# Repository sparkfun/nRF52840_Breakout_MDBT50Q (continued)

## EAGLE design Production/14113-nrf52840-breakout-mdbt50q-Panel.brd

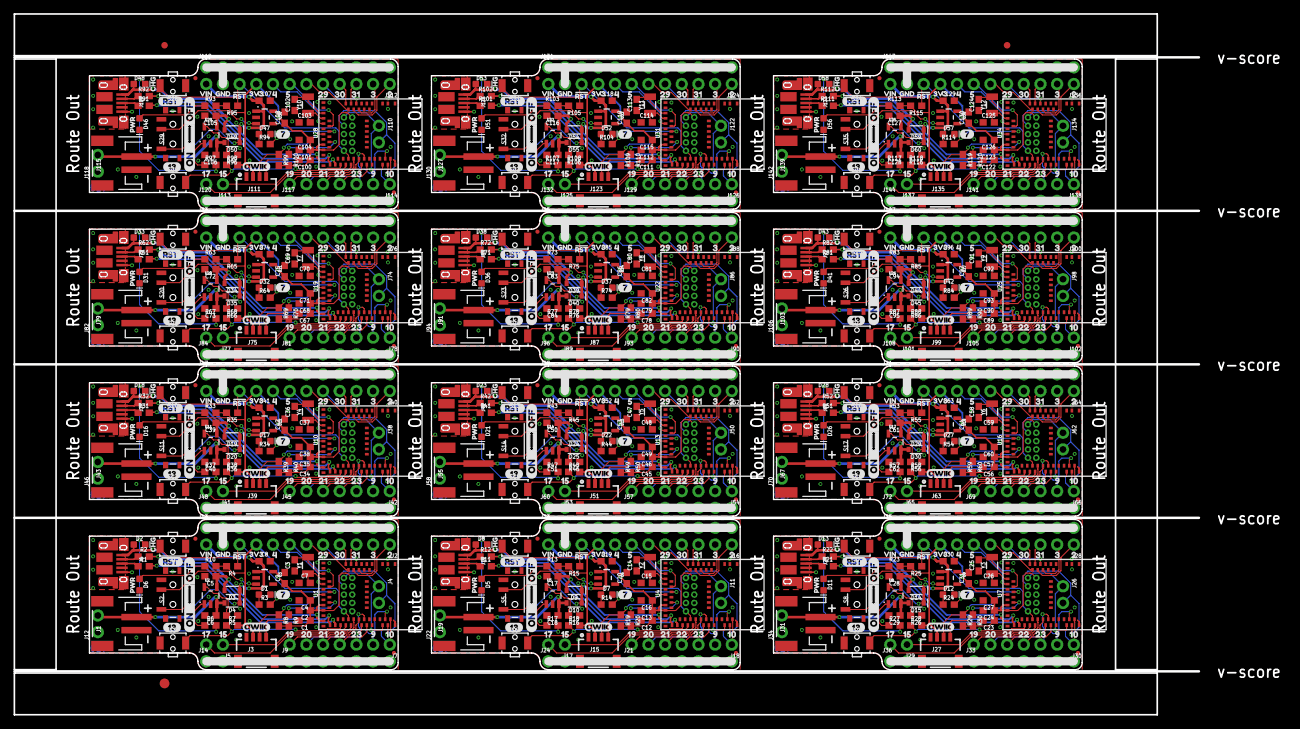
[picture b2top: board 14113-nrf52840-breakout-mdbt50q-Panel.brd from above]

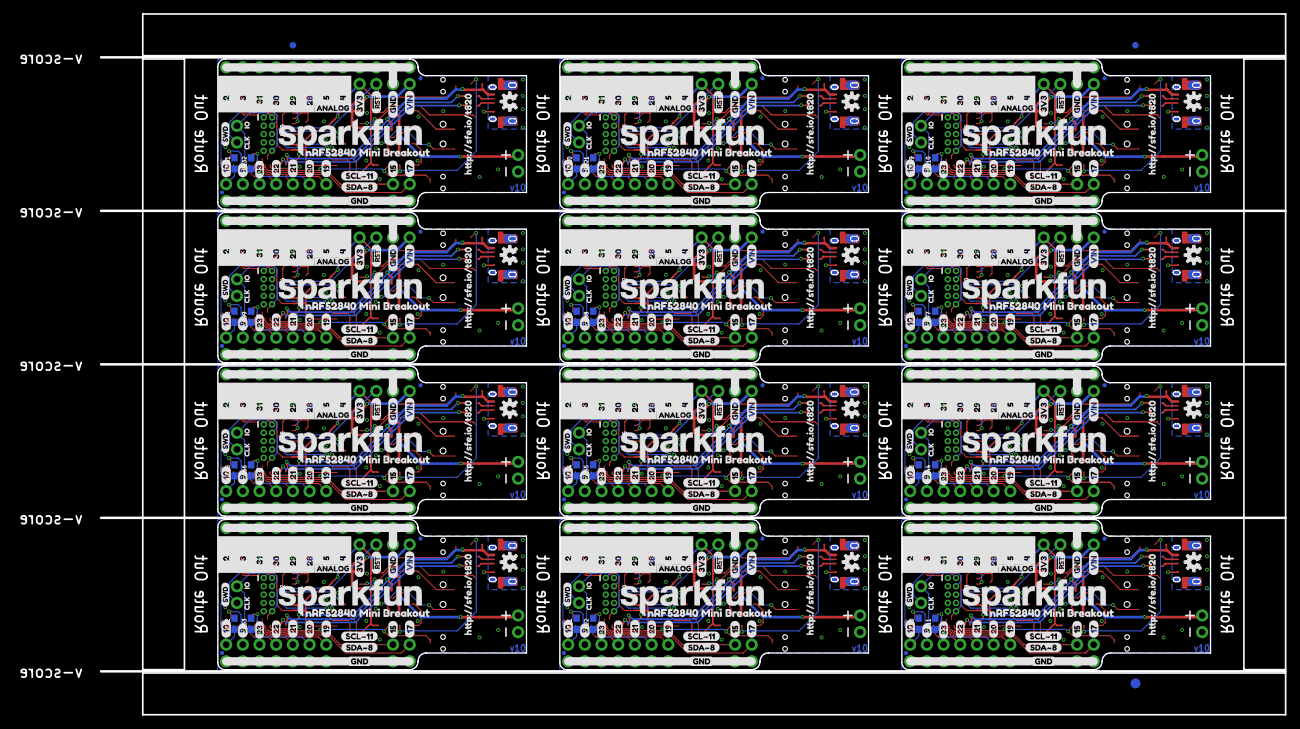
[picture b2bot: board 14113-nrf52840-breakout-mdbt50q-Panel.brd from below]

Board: 2 copper layers, 180.3 x 106.7 mm, 1314 parts (447 on the bottom side), 504 nets.

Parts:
C1, C4, C12, C16, C23, C27, C34, C38, C45, C49, C56, C60, C67, C71, C78, C82, C89, C93, C100, C104, C111, C115, C122, C126: 10uF; 0603
C2, C13, C24, C35, C46, C57, C68, C79, C90, C101, C112, C123: 0.1uF; 0603
C3, C7, C14, C15, C25, C26, C36, C37, C47, C48, C58, C59, C69, C70, C80, C81, C91, C92, C102, C103, C113, C114, C124, C125: 15pF; 0603
C5, C6, C17, C18, C28, C29, C39, C40, C50, C51, C61, C62, C72, C73, C83, C84, C94, C95, C105, C106, C116, C117, C127, C128: 4.7uF; 0603
C8, C9, C19, C20, C30, C31, C41, C42, C52, C53, C63, C64, C74, C75, C85, C86, C96, C97, C107, C108, C118, C119, C129, C130: 1.0uF; 0603
C10, C11, C21, C22, C32, C33, C43, C44, C54, C55, C65, C66, C76, C77, C87, C88, C98, C99, C109, C110, C120, C121, C131, C132: DNP; 0603
D1, D7, D12, D17, D22, D27, D32, D37, D42, D47, D52, D57: BLUE; LED-0603
D2, D8, D13, D18, D23, D28, D33, D38, D43, D48, D53, D58: Yellow; LED-0603
D3, D4, D9, D10, D14, D15, D19, D20, D24, D25, D29, D30, D34, D35, D39, D40, D44, D45, D49, D50, D54, D55, D59, D60: 1A/23V/620mV; SOD-323
D5, D6, D11, D16, D21, D26, D31, D36, D41, D46, D51, D56: RED; LED-0603
E$1, E$2, E$3, E$4: FIDUCIAL-1X2
E$5, E$6: FIDUCIAL-1.5X3
FD1, FD2, FD3, FD4, FD5, FD6, FD7, FD8, FD9, FD10, FD11, FD12, FD13, FD14, FD15, FD16, FD17, FD18, FD19, FD20, FD21, FD22, FD23, FD24, FD25, FD26, FD27, FD28, FD29, FD30, FD31, FD32, FD33, FD34, FD35, FD36, FD37, FD38, FD39, FD40, FD41, FD42, FD43, FD44, FD45, FD46, FD47, FD48: FIDUCIALUFIDUCIAL; FIDUCIAL-MICRO
J1, J19, J31, J43, J55, J67, J79, J91, J103, J115, J127, J139: JST-2-SMD
J2, J13, J16, J23, J28, J35, J40, J47, J52, J59, J64, J71, J76, J83, J88, J95, J100, J107, J112, J119, J124, J131, J136, J143: 1X12_NO_SILK
J3, J15, J27, J39, J51, J63, J75, J87, J99, J111, J123, J135: 1X04_1MM_RA
J4, J5, J11, J12, J14, J17, J22, J24, J26, J29, J34, J36, J38, J41, J46, J48, J50, J53, J58, J60, J62, J65, J70, J72, J74, J77, J82, J84, J86, J89, J94, J96, J98, J101, J106, J108, J110, J113, J118, J120, J122, J125, J130, J132, J134, J137, J142, J144: 1X02_NO_SILK
J6, J10, J25, J37, J49, J61, J73, J85, J97, J109, J121, J133: USB-MICROB-PTH-MILL
J7, J9, J18, J21, J30, J33, J42, J45, J54, J57, J66, J69, J78, J81, J90, J93, J102, J105, J114, J117, J126, J129, J138, J141: 1X07_NO_SILK
J8, J20, J32, J44, J56, J68, J80, J92, J104, J116, J128, J140: CORTEX_DEBUG_PTH; 2X5-PTH-1.27MM
LOGO1, LOGO3, LOGO5, LOGO7, LOGO9, LOGO11, LOGO13, LOGO15, LOGO17, LOGO19, LOGO21, LOGO23: SFE_LOGO_NAME.2_INCH; SFE_LOGO_NAME_.2
LOGO2, LOGO4, LOGO6, LOGO8, LOGO10, LOGO12, LOGO14, LOGO16, LOGO18, LOGO20, LOGO22, LOGO24: OSHW-LOGOS; OSHW-LOGO-S
R1, R2, R11, R12, R21, R22, R31, R32, R41, R42, R51, R52, R61, R62, R71, R72, R81, R82, R91, R92, R101, R102, R111, R112: 27; 0603
R3, R6, R10, R13, R14, R17, R23, R24, R27, R33, R34, R37, R43, R44, R47, R53, R54, R57, R63, R64, R67, R73, R74, R77, R83, R84, R87, R93, R94, R97, R103, R104, R107, R113, R114, R117: 1k; 0603
R4, R7, R15, R18, R25, R28, R35, R38, R45, R48, R55, R58, R65, R68, R75, R78, R85, R88, R95, R98, R105, R108, R115, R118: 10k; 0603
R5, R16, R26, R36, R46, R56, R66, R76, R86, R96, R106, R116: 2.0k; 0603
R8, R9, R19, R20, R29, R30, R39, R40, R49, R50, R59, R60, R69, R70, R79, R80, R89, R90, R99, R100, R109, R110, R119, R120: 2.2k; 0603
S1, S4, S7, S10, S13, S16, S19, S22, S25, S28, S31, S34: RESET; TACTILE_SWITCH_SMD_RIGHT_ANGLE
S2, S5, S8, S11, S14, S17, S20, S23, S26, S29, S32, S35: SWITCH_SPST_SMD_A
S3, S6, S9, S12, S15, S18, S21, S24, S27, S30, S33, S36: BOOTLOAD; TACTILE_SWITCH_SMD_RIGHT_ANGLE
U1, U4, U7, U10, U13, U16, U19, U22, U25, U28, U31, U34: MDBT50Q
U2, U5, U8, U11, U14, U17, U20, U23, U26, U29, U32, U35: MCP73831; SOT23-5
U3, U6, U9, U12, U15, U18, U21, U24, U27, U30, U33, U36: 3.3V; SOT23-5
U$1, U$92, U$150, U$208, U$266, U$324, U$382, U$440, U$498, U$556, U$614, U$672: 3V316
U$2, U$109, U$167, U$225, U$283, U$341, U$399, U$457, U$515, U$573, U$631, U$689: 130
U$3, U$91, U$149, U$207, U$265, U$323, U$381, U$439, U$497, U$555, U$613, U$671: RST19
U$4, U$113, U$171, U$229, U$287, U$345, U$403, U$461, U$519, U$577, U$635, U$693: ON1
U$5, U$59, U$117, U$175, U$233, U$291, U$349, U$407, U$465, U$523, U$581, U$639: CHG26
U$6, U$60, U$118, U$176, U$234, U$292, U$350, U$408, U$466, U$524, U$582, U$640: PWR27
U$7, U$89, U$147, U$205, U$263, U$321, U$379, U$437, U$495, U$553, U$611, U$669: GND17
U$8, U$87, U$145, U$203, U$261, U$319, U$377, U$435, U$493, U$551, U$609, U$667: QWIIC#LOGO#JPG
U$9, U$62, U$120, U$178, U$236, U$294, U$352, U$410, U$468, U$526, U$584, U$642: 20
U$10, U$63, U$121, U$179, U$237, U$295, U$353, U$411, U$469, U$527, U$585, U$643: 31
U$11, U$64, U$122, U$180, U$238, U$296, U$354, U$412, U$470, U$528, U$586, U$644: 292
U$12, U$65, U$123, U$181, U$239, U$297, U$355, U$413, U$471, U$529, U$587, U$645: 313
U$13, U$111, U$169, U$227, U$285, U$343, U$401, U$459, U$517, U$575, U$633, U$691: 3V30
U$14, U$66, U$124, U$182, U$240, U$298, U$356, U$414, U$472, U$530, U$588, U$646: 285
U$15, U$67, U$125, U$183, U$241, U$299, U$357, U$415, U$473, U$531, U$589, U$647: 521
U$16, U$68, U$126, U$184, U$242, U$300, U$358, U$416, U$474, U$532, U$590, U$648: 421
U$17, U$112, U$170, U$228, U$286, U$344, U$402, U$460, U$518, U$576, U$634, U$692: HTTP###SFE#IO#T8200
U$18, U$69, U$127, U$185, U$243, U$301, U$359, U$417, U$475, U$533, U$591, U$649: #RST6
U$19, U$70, U$128, U$186, U$244, U$302, U$360, U$418, U$476, U$534, U$592, U$650: GND7
U$20, U$71, U$129, U$187, U$245, U$303, U$361, U$419, U$477, U$535, U$593, U$651: VIN8
U$21, U$72, U$130, U$188, U$246, U$304, U$362, U$420, U$478, U$536, U$594, U$652: 1022
U$22, U$73, U$131, U$189, U$247, U$305, U$363, U$421, U$479, U$537, U$595, U$653: 916
U$23, U$74, U$132, U$190, U$248, U$306, U$364, U$422, U$480, U$538, U$596, U$654: 2111
U$24, U$75, U$133, U$191, U$249, U$307, U$365, U$423, U$481, U$539, U$597, U$655: 1912
U$25, U$76, U$134, U$192, U$250, U$308, U$366, U$424, U$482, U$540, U$598, U$656: 1713
U$26, U$77, U$135, U$193, U$251, U$309, U$367, U$425, U$483, U$541, U$599, U$657: 1522
U$27, U$90, U$148, U$206, U$264, U$322, U$380, U$438, U$496, U$554, U$612, U$670: VIN19
U$28, U$88, U$146, U$204, U$262, U$320, U$378, U$436, U$494, U$552, U$610, U$668: 70
U$29, U$86, U$144, U$202, U$260, U$318, U$376, U$434, U$492, U$550, U$608, U$666: NRF52840_MINI_BREAKOUT0
U$30, U$61, U$119, U$177, U$235, U$293, U$351, U$409, U$467, U$525, U$583, U$641: GND6
U$31, U$93, U$151, U$209, U$267, U$325, U$383, U$441, U$499, U$557, U$615, U$673: 27
U$32, U$94, U$152, U$210, U$268, U$326, U$384, U$442, U$500, U$558, U$616, U$674: 36
U$33, U$83, U$141, U$199, U$257, U$315, U$373, U$431, U$489, U$547, U$605, U$663: SWD0
U$34, U$95, U$153, U$211, U$269, U$327, U$385, U$443, U$501, U$559, U$617, U$675: 315
U$35, U$110, U$168, U$226, U$284, U$342, U$400, U$458, U$516, U$574, U$632, U$690: 300
U$36, U$116, U$174, U$232, U$290, U$348, U$406, U$464, U$522, U$580, U$638, U$696: 301
U$37, U$96, U$154, U$212, U$270, U$328, U$386, U$444, U$502, U$560, U$618, U$676: 293
U$38, U$99, U$157, U$215, U$273, U$331, U$389, U$447, U$505, U$563, U$621, U$679: 108
U$39, U$97, U$155, U$213, U$271, U$329, U$387, U$445, U$503, U$561, U$619, U$677: 51
U$40, U$98, U$156, U$214, U$272, U$330, U$388, U$446, U$504, U$562, U$620, U$678: 40
U$41, U$100, U$158, U$216, U$274, U$332, U$390, U$448, U$506, U$564, U$622, U$680: 97
U$42, U$101, U$159, U$217, U$275, U$333, U$391, U$449, U$507, U$565, U$623, U$681: 236
U$43, U$78, U$136, U$194, U$252, U$310, U$368, U$426, U$484, U$542, U$600, U$658: 200
U$44, U$102, U$160, U$218, U$276, U$334, U$392, U$450, U$508, U$566, U$624, U$682: 225
U$45, U$79, U$137, U$195, U$253, U$311, U$369, U$427, U$485, U$543, U$601, U$659: 221
U$46, U$103, U$161, U$219, U$277, U$335, U$393, U$451, U$509, U$567, U$625, U$683: 214
U$47, U$104, U$162, U$220, U$278, U$336, U$394, U$452, U$510, U$568, U$626, U$684: 203
U$48, U$105, U$163, U$221, U$279, U$337, U$395, U$453, U$511, U$569, U$627, U$685: 192
U$49, U$106, U$164, U$222, U$280, U$338, U$396, U$454, U$512, U$570, U$628, U$686: 151
U$50, U$107, U$165, U$223, U$281, U$339, U$397, U$455, U$513, U$571, U$629, U$687: 170
U$51, U$108, U$166, U$224, U$282, U$340, U$398, U$456, U$514, U$572, U$630, U$688: RST1
U$52, U$115, U$173, U$231, U$289, U$347, U$405, U$463, U$521, U$579, U$637, U$695: ANALOG2
U$53, U$80, U$138, U$196, U$254, U$312, U$370, U$428, U$486, U$544, U$602, U$660: 232
U$54, U$81, U$139, U$197, U$255, U$313, U$371, U$429, U$487, U$545, U$603, U$661: SCL#114
U$55, U$82, U$140, U$198, U$256, U$314, U$372, U$430, U$488, U$546, U$604, U$662: SDA#83
U$56, U$84, U$142, U$200, U$258, U$316, U$374, U$432, U$490, U$548, U$606, U$664: IO2
U$57, U$85, U$143, U$201, U$259, U$317, U$375, U$433, U$491, U$549, U$607, U$665: CLK1
U$58, U$114, U$172, U$230, U$288, U$346, U$404, U$462, U$520, U$578, U$636, U$694: OFF2
Y1, Y2, Y3, Y4, Y5, Y6, Y7, Y8, Y9, Y10, Y11, Y12: 32.768kHz; CRYSTAL-SMD-3.2X1.5MM

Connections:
3.3V: C1.1, C2.1, C4.1, C9.1, J2.9, J3.2, J8.1, R4.2, R7.2, R8.2, R9.2, R10.2, U1.28, U1.30, U3.5
3.3V1: C12.1, C13.1, C16.1, C20.1, J15.2, J16.9, J20.1, R13.2, R15.2, R18.2, R19.2, R20.2, U4.28, U4.30, U6.5
3.3V2: C23.1, C24.1, C27.1, C31.1, J27.2, J28.9, J32.1, R23.2, R25.2, R28.2, R29.2, R30.2, U7.28, U7.30, U9.5
3.3V3: C34.1, C35.1, C38.1, C42.1, J39.2, J40.9, J44.1, R33.2, R35.2, R38.2, R39.2, R40.2, U10.28, U10.30, U12.5
3.3V4: C45.1, C46.1, C49.1, C53.1, J51.2, J52.9, J56.1, R43.2, R45.2, R48.2, R49.2, R50.2, U13.28, U13.30, U15.5
3.3V5: C56.1, C57.1, C60.1, C64.1, J63.2, J64.9, J68.1, R53.2, R55.2, R58.2, R59.2, R60.2, U16.28, U16.30, U18.5
3.3V6: C67.1, C68.1, C71.1, C75.1, J75.2, J76.9, J80.1, R63.2, R65.2, R68.2, R69.2, R70.2, U19.28, U19.30, U21.5
3.3V7: C78.1, C79.1, C82.1, C86.1, J87.2, J88.9, J92.1, R73.2, R75.2, R78.2, R79.2, R80.2, U22.28, U22.30, U24.5
3.3V8: C89.1, C90.1, C93.1, C97.1, J99.2, J100.9, J104.1, R83.2, R85.2, R88.2, R89.2, R90.2, U25.28, U25.30, U27.5
3.3V9: C100.1, C101.1, C104.1, C108.1, J111.2, J112.9, J116.1, R93.2, R95.2, R98.2, R99.2, R100.2, U28.28, U28.30, U30.5
3.3V10: C111.1, C112.1, C115.1, C119.1, J123.2, J124.9, J128.1, R103.2, R105.2, R108.2, R109.2, R110.2, U31.28, U31.30, U33.5
3.3V11: C122.1, C123.1, C126.1, C130.1, J135.2, J136.9, J140.1, R113.2, R115.2, R118.2, R119.2, R120.2, U34.28, U34.30, U36.5
!RESET: J2.10, J8.10, R4.1, S1.2, U1.40
!RESET1: J16.10, J20.10, R15.1, S4.2, U4.40
!RESET2: J28.10, J32.10, R25.1, S7.2, U7.40
!RESET3: J40.10, J44.10, R35.1, S10.2, U10.40
!RESET4: J52.10, J56.10, R45.1, S13.2, U13.40
!RESET5: J64.10, J68.10, R55.1, S16.2, U16.40
!RESET6: J76.10, J80.10, R65.1, S19.2, U19.40
!RESET7: J88.10, J92.10, R75.1, S22.2, U22.40
!RESET8: J100.10, J104.10, R85.1, S25.2, U25.40
!RESET9: J112.10, J116.10, R95.1, S28.2, U28.40
!RESET10: J124.10, J128.10, R105.1, S31.2, U31.40
!RESET11: J136.10, J140.10, R115.1, S34.2, U34.40
D+: R1.2, U1.35
D+1: R11.2, U4.35
D+2: R21.2, U7.35
D+3: R31.2, U10.35
D+4: R41.2, U13.35
D+5: R51.2, U16.35
D+6: R61.2, U19.35
D+7: R71.2, U22.35
D+8: R81.2, U25.35
D+9: R91.2, U28.35
D+10: R101.2, U31.35
D+11: R111.2, U34.35
D+_CON: J6.D+, R1.1
D+_CON1: J10.D+, R11.1
D+_CON2: J25.D+, R21.1
D+_CON3: J37.D+, R31.1
D+_CON4: J49.D+, R41.1
D+_CON5: J61.D+, R51.1
D+_CON6: J73.D+, R61.1
D+_CON7: J85.D+, R71.1
D+_CON8: J97.D+, R81.1
D+_CON9: J109.D+, R91.1
D+_CON10: J121.D+, R101.1
D+_CON11: J133.D+, R111.1
D-: R2.2, U1.34
D-1: R12.2, U4.34
D-2: R22.2, U7.34
D-3: R32.2, U10.34
D-4: R42.2, U13.34
D-5: R52.2, U16.34
D-6: R62.2, U19.34
D-7: R72.2, U22.34
D-8: R82.2, U25.34
D-9: R92.2, U28.34
D-10: R102.2, U31.34
D-11: R112.2, U34.34
D-_CON: J6.D-, R2.1
D-_CON1: J10.D-, R12.1
D-_CON2: J25.D-, R22.1
D-_CON3: J37.D-, R32.1
D-_CON4: J49.D-, R42.1
D-_CON5: J61.D-, R52.1
D-_CON6: J73.D-, R62.1
D-_CON7: J85.D-, R72.1
D-_CON8: J97.D-, R82.1
D-_CON9: J109.D-, R92.1
D-_CON10: J121.D-, R102.1
D-_CON11: J133.D-, R112.1
GND: C1.2, C2.2, C3.1, C4.2, C5.2, C6.2, C7.1, C8.2, C9.2, C10.2, C11.2, D1.C, D6.C, J1.1, J2.11, J3.1, J6.GND, J8.3, J8.5, J8.9, J9.1, J9.2, J9.3, J9.4, J9.5, J9.6, J9.7, J12.1, J13.1, J13.2, J13.3, J13.4, J13.5, J13.6, J13.7, J13.8, J13.9, J13.10, J13.11, J13.12, J14.1, J14.2, R5.1, S1.1, S2.1, S3.1, U1.1, U1.2, U1.15, U1.33, U1.55, U2.2, U3.2
GND1: C12.2, C13.2, C14.1, C15.1, C16.2, C17.2, C18.2, C19.2, C20.2, C21.2, C22.2, D5.C, D7.C, J10.GND, J15.1, J16.11, J19.1, J20.3, J20.5, J20.9, J21.1, J21.2, J21.3, J21.4, J21.5, J21.6, J21.7, J22.1, J23.1, J23.2, J23.3, J23.4, J23.5, J23.6, J23.7, J23.8, J23.9, J23.10, J23.11, J23.12, J24.1, J24.2, R16.1, S4.1, S5.1, S6.1, U4.1, U4.2, U4.15, U4.33, U4.55, U5.2, U6.2
GND2: C23.2, C24.2, C25.1, C26.1, C27.2, C28.2, C29.2, C30.2, C31.2, C32.2, C33.2, D11.C, D12.C, J25.GND, J27.1, J28.11, J31.1, J32.3, J32.5, J32.9, J33.1, J33.2, J33.3, J33.4, J33.5, J33.6, J33.7, J34.1, J35.1, J35.2, J35.3, J35.4, J35.5, J35.6, J35.7, J35.8, J35.9, J35.10, J35.11, J35.12, J36.1, J36.2, R26.1, S7.1, S8.1, S9.1, U7.1, U7.2, U7.15, U7.33, U7.55, U8.2, U9.2
GND3: C34.2, C35.2, C36.1, C37.1, C38.2, C39.2, C40.2, C41.2, C42.2, C43.2, C44.2, D16.C, D17.C, J37.GND, J39.1, J40.11, J43.1, J44.3, J44.5, J44.9, J45.1, J45.2, J45.3, J45.4, J45.5, J45.6, J45.7, J46.1, J47.1, J47.2, J47.3, J47.4, J47.5, J47.6, J47.7, J47.8, J47.9, J47.10, J47.11, J47.12, J48.1, J48.2, R36.1, S10.1, S11.1, S12.1, U10.1, U10.2, U10.15, U10.33, U10.55, U11.2, U12.2
GND4: C45.2, C46.2, C47.1, C48.1, C49.2, C50.2, C51.2, C52.2, C53.2, C54.2, C55.2, D21.C, D22.C, J49.GND, J51.1, J52.11, J55.1, J56.3, J56.5, J56.9, J57.1, J57.2, J57.3, J57.4, J57.5, J57.6, J57.7, J58.1, J59.1, J59.2, J59.3, J59.4, J59.5, J59.6, J59.7, J59.8, J59.9, J59.10, J59.11, J59.12, J60.1, J60.2, R46.1, S13.1, S14.1, S15.1, U13.1, U13.2, U13.15, U13.33, U13.55, U14.2, U15.2
GND5: C56.2, C57.2, C58.1, C59.1, C60.2, C61.2, C62.2, C63.2, C64.2, C65.2, C66.2, D26.C, D27.C, J61.GND, J63.1, J64.11, J67.1, J68.3, J68.5, J68.9, J69.1, J69.2, J69.3, J69.4, J69.5, J69.6, J69.7, J70.1, J71.1, J71.2, J71.3, J71.4, J71.5, J71.6, J71.7, J71.8, J71.9, J71.10, J71.11, J71.12, J72.1, J72.2, R56.1, S16.1, S17.1, S18.1, U16.1, U16.2, U16.15, U16.33, U16.55, U17.2, U18.2
GND6: C67.2, C68.2, C69.1, C70.1, C71.2, C72.2, C73.2, C74.2, C75.2, C76.2, C77.2, D31.C, D32.C, J73.GND, J75.1, J76.11, J79.1, J80.3, J80.5, J80.9, J81.1, J81.2, J81.3, J81.4, J81.5, J81.6, J81.7, J82.1, J83.1, J83.2, J83.3, J83.4, J83.5, J83.6, J83.7, J83.8, J83.9, J83.10, J83.11, J83.12, J84.1, J84.2, R66.1, S19.1, S20.1, S21.1, U19.1, U19.2, U19.15, U19.33, U19.55, U20.2, U21.2
GND7: C78.2, C79.2, C80.1, C81.1, C82.2, C83.2, C84.2, C85.2, C86.2, C87.2, C88.2, D36.C, D37.C, J85.GND, J87.1, J88.11, J91.1, J92.3, J92.5, J92.9, J93.1, J93.2, J93.3, J93.4, J93.5, J93.6, J93.7, J94.1, J95.1, J95.2, J95.3, J95.4, J95.5, J95.6, J95.7, J95.8, J95.9, J95.10, J95.11, J95.12, J96.1, J96.2, R76.1, S22.1, S23.1, S24.1, U22.1, U22.2, U22.15, U22.33, U22.55, U23.2, U24.2
GND8: C89.2, C90.2, C91.1, C92.1, C93.2, C94.2, C95.2, C96.2, C97.2, C98.2, C99.2, D41.C, D42.C, J97.GND, J99.1, J100.11, J103.1, J104.3, J104.5, J104.9, J105.1, J105.2, J105.3, J105.4, J105.5, J105.6, J105.7, J106.1, J107.1, J107.2, J107.3, J107.4, J107.5, J107.6, J107.7, J107.8, J107.9, J107.10, J107.11, J107.12, J108.1, J108.2, R86.1, S25.1, S26.1, S27.1, U25.1, U25.2, U25.15, U25.33, U25.55, U26.2, U27.2
GND9: C100.2, C101.2, C102.1, C103.1, C104.2, C105.2, C106.2, C107.2, C108.2, C109.2, C110.2, D46.C, D47.C, J109.GND, J111.1, J112.11, J115.1, J116.3, J116.5, J116.9, J117.1, J117.2, J117.3, J117.4, J117.5, J117.6, J117.7, J118.1, J119.1, J119.2, J119.3, J119.4, J119.5, J119.6, J119.7, J119.8, J119.9, J119.10, J119.11, J119.12, J120.1, J120.2, R96.1, S28.1, S29.1, S30.1, U28.1, U28.2, U28.15, U28.33, U28.55, U29.2, U30.2
GND10: C111.2, C112.2, C113.1, C114.1, C115.2, C116.2, C117.2, C118.2, C119.2, C120.2, C121.2, D51.C, D52.C, J121.GND, J123.1, J124.11, J127.1, J128.3, J128.5, J128.9, J129.1, J129.2, J129.3, J129.4, J129.5, J129.6, J129.7, J130.1, J131.1, J131.2, J131.3, J131.4, J131.5, J131.6, J131.7, J131.8, J131.9, J131.10, J131.11, J131.12, J132.1, J132.2, R106.1, S31.1, S32.1, S33.1, U31.1, U31.2, U31.15, U31.33, U31.55, U32.2, U33.2
GND11: C122.2, C123.2, C124.1, C125.1, C126.2, C127.2, C128.2, C129.2, C130.2, C131.2, C132.2, D56.C, D57.C, J133.GND, J135.1, J136.11, J139.1, J140.3, J140.5, J140.9, J141.1, J141.2, J141.3, J141.4, J141.5, J141.6, J141.7, J142.1, J143.1, J143.2, J143.3, J143.4, J143.5, J143.6, J143.7, J143.8, J143.9, J143.10, J143.11, J143.12, J144.1, J144.2, R116.1, S34.1, S35.1, S36.1, U34.1, U34.2, U34.15, U34.33, U34.55, U35.2, U36.2
unnamed: R5.2, U2.5
unnamed: D5.A, R13.1
unnamed: D2.C, R6.2
unnamed: R6.1, U2.1
unnamed: D7.A, R14.1
unnamed: R16.2, U5.5
unnamed: D1.A, R3.1
unnamed: D8.C, R17.2
unnamed: R17.1, U5.1
unnamed: D6.A, R10.1
unnamed: D11.A, R23.1
unnamed: D12.A, R24.1
unnamed: R26.2, U8.5
unnamed: D13.C, R27.2
unnamed: R27.1, U8.1
unnamed: D16.A, R33.1
unnamed: D17.A, R34.1
unnamed: R36.2, U11.5
unnamed: D18.C, R37.2
unnamed: R37.1, U11.1
unnamed: D21.A, R43.1
unnamed: D22.A, R44.1
unnamed: R46.2, U14.5
unnamed: D23.C, R47.2
unnamed: R47.1, U14.1
unnamed: D26.A, R53.1
unnamed: D27.A, R54.1
unnamed: R56.2, U17.5
unnamed: D28.C, R57.2
unnamed: R57.1, U17.1
unnamed: D31.A, R63.1
unnamed: D32.A, R64.1
unnamed: R66.2, U20.5
unnamed: D33.C, R67.2
unnamed: R67.1, U20.1
unnamed: D36.A, R73.1
unnamed: D37.A, R74.1
unnamed: R76.2, U23.5
unnamed: D38.C, R77.2
unnamed: R77.1, U23.1
unnamed: D41.A, R83.1
unnamed: D42.A, R84.1
unnamed: R86.2, U26.5
unnamed: D43.C, R87.2
unnamed: R87.1, U26.1
unnamed: D46.A, R93.1
unnamed: D47.A, R94.1
unnamed: R96.2, U29.5
unnamed: D48.C, R97.2
unnamed: R97.1, U29.1
unnamed: D51.A, R103.1
unnamed: D52.A, R104.1
unnamed: R106.2, U32.5
unnamed: D53.C, R107.2
unnamed: R107.1, U32.1
unnamed: D56.A, R113.1
unnamed: D57.A, R114.1
unnamed: R116.2, U35.5
unnamed: D58.C, R117.2
unnamed: R117.1, U35.1
P0.01: R18.1, S6.2, U4.37
P0.02: J17.1, U4.39
P0.02/AIN0: J2.1, U1.11
P0.02/AIN1: J16.1, U4.11
P0.02/AIN2: J28.1, U7.11
P0.02/AIN3: J40.1, U10.11
P0.02/AIN4: J52.1, U13.11
P0.02/AIN5: J64.1, U16.11
P0.02/AIN6: J76.1, U19.11
P0.02/AIN7: J88.1, U22.11
P0.02/AIN8: J100.1, U25.11
P0.02/AIN9: J112.1, U28.11
P0.02/AIN10: J124.1, U31.11
P0.02/AIN11: J136.1, U34.11
P0.03: J17.2, U4.41
P0.03/AIN1: J2.2, U1.9
P0.03/AIN2: J16.2, U4.9
P0.03/AIN3: J28.2, U7.9
P0.03/AIN4: J40.2, U10.9
P0.03/AIN5: J52.2, U13.9
P0.03/AIN6: J64.2, U16.9
P0.03/AIN7: J76.2, U19.9
P0.03/AIN8: J88.2, U22.9
P0.03/AIN9: J100.2, U25.9
P0.03/AIN10: J112.2, U28.9
P0.03/AIN11: J124.2, U31.9
P0.03/AIN12: J136.2, U34.9
P0.04: J18.7, U4.42
P0.04/AIN1: J16.8, U4.20
P0.04/AIN2: J2.8, U1.20
P0.04/AIN3: J28.8, U7.20
P0.04/AIN4: J40.8, U10.20
P0.04/AIN5: J52.8, U13.20
P0.04/AIN6: J64.8, U16.20
P0.04/AIN7: J76.8, U19.20
P0.04/AIN8: J88.8, U22.20
P0.04/AIN9: J100.8, U25.20
P0.04/AIN10: J112.8, U28.20
P0.04/AIN11: J124.8, U31.20
P0.04/AIN12: J136.8, U34.20
P0.05: J18.6, U4.44
P0.05/AIN1: J16.7, U4.21
P0.05/AIN2: J28.7, U7.21
P0.05/AIN3: J2.7, U1.21
P0.05/AIN4: J40.7, U10.21
P0.05/AIN5: J52.7, U13.21
P0.05/AIN6: J64.7, U16.21
P0.05/AIN7: J76.7, U19.21
P0.05/AIN8: J88.7, U22.21
P0.05/AIN9: J100.7, U25.21
P0.05/AIN10: J112.7, U28.21
P0.05/AIN11: J124.7, U31.21
P0.05/AIN12: J136.7, U34.21
P0.07: R3.2, U1.23
P0.08: J3.3, R8.1, U1.24
P0.09: J18.5, U4.43
P0.09/NFC1: C11.1, J7.2, U1.52
P0.09/NFC2: C22.1, J18.2, U4.52
P0.09/NFC3: C33.1, J30.2, U7.52
P0.09/NFC4: C44.1, J42.2, U10.52
P0.09/NFC5: C55.1, J54.2, U13.52
P0.09/NFC6: C66.1, J66.2, U16.52
P0.09/NFC7: C77.1, J78.2, U19.52
P0.09/NFC8: C88.1, J90.2, U22.52
P0.09/NFC9: C99.1, J102.2, U25.52
P0.09/NFC10: C110.1, J114.2, U28.52
P0.09/NFC11: C121.1, J126.2, U31.52
P0.09/NFC12: C132.1, J138.2, U34.52
P0.10: J18.4, U4.46
P0.10/NFC1: C21.1, J18.1, U4.54
P0.10/NFC2: C10.1, J7.1, U1.54
P0.10/NFC3: C32.1, J30.1, U7.54
P0.10/NFC4: C43.1, J42.1, U10.54
P0.10/NFC5: C54.1, J54.1, U13.54
P0.10/NFC6: C65.1, J66.1, U16.54
P0.10/NFC7: C76.1, J78.1, U19.54
P0.10/NFC8: C87.1, J90.1, U22.54
P0.10/NFC9: C98.1, J102.1, U25.54
P0.10/NFC10: C109.1, J114.1, U28.54
P0.10/NFC11: C120.1, J126.1, U31.54
P0.10/NFC12: C131.1, J138.1, U34.54
P0.11: J3.4, R9.1, U1.27
P0.12: J18.3, U4.45
P0.13: R7.1, S3.2, U1.37
P0.15: J5.1, U1.39
P0.16: J15.3, R19.1, U4.24
P0.17: J5.2, U1.41
P0.18: J15.4, R20.1, U4.27
P0.19: J7.7, U1.42
P0.20: J7.6, U1.44
P0.21: J7.5, U1.43
P0.22: J7.4, U1.46
P0.23: J7.3, U1.45
P0.24: R14.2, U4.23
P0.25: R28.1, S9.2, U7.37
P0.26: J29.1, U7.39
P0.27: J29.2, U7.41
P0.28: J30.7, U7.42
P0.28/AIN1: J16.6, U4.13
P0.28/AIN2: J28.6, U7.13
P0.28/AIN3: J40.6, U10.13
P0.28/AIN4: J2.6, U1.13
P0.28/AIN5: J52.6, U13.13
P0.28/AIN6: J64.6, U16.13
P0.28/AIN7: J76.6, U19.13
P0.28/AIN8: J88.6, U22.13
P0.28/AIN9: J100.6, U25.13
P0.28/AIN10: J112.6, U28.13
P0.28/AIN11: J124.6, U31.13
P0.28/AIN12: J136.6, U34.13
P0.29: J30.6, U7.44
P0.29/AIN1: J16.5, U4.10
P0.29/AIN2: J28.5, U7.10
P0.29/AIN3: J40.5, U10.10
P0.29/AIN4: J52.5, U13.10
P0.29/AIN5: J2.5, U1.10
P0.29/AIN6: J64.5, U16.10
P0.29/AIN7: J76.5, U19.10
P0.29/AIN8: J88.5, U22.10
P0.29/AIN9: J100.5, U25.10
P0.29/AIN10: J112.5, U28.10
P0.29/AIN11: J124.5, U31.10
P0.29/AIN12: J136.5, U34.10
P0.30: J30.5, U7.43
P0.30/AIN1: J16.4, U4.14
P0.30/AIN2: J28.4, U7.14
P0.30/AIN3: J40.4, U10.14
P0.30/AIN4: J52.4, U13.14
P0.30/AIN5: J64.4, U16.14
P0.30/AIN6: J2.4, U1.14
P0.30/AIN7: J76.4, U19.14
P0.30/AIN8: J88.4, U22.14
P0.30/AIN9: J100.4, U25.14
P0.30/AIN10: J112.4, U28.14
P0.30/AIN11: J124.4, U31.14
P0.30/AIN12: J136.4, U34.14
P0.31: J30.4, U7.46
P0.31/AIN1: J16.3, U4.12
P0.31/AIN2: J28.3, U7.12
P0.31/AIN3: J40.3, U10.12
P0.31/AIN4: J52.3, U13.12
P0.31/AIN5: J64.3, U16.12
P0.31/AIN6: J76.3, U19.12
P0.31/AIN7: J2.3, U1.12
P0.31/AIN8: J88.3, U22.12
P0.31/AIN9: J100.3, U25.12
P0.31/AIN10: J112.3, U28.12
P0.31/AIN11: J124.3, U31.12
P0.31/AIN12: J136.3, U34.12
P0.32: J30.3, U7.45
P0.34: J27.3, R29.1, U7.24
P0.35: J27.4, R30.1, U7.27
P0.36: R24.2, U7.23
P0.37: R38.1, S12.2, U10.37
P0.38: J41.1, U10.39
P0.39: J41.2, U10.41
P0.40: J42.7, U10.42
P0.41: J42.6, U10.44
P0.42: J42.5, U10.43
P0.43: J42.4, U10.46
P0.44: J42.3, U10.45
P0.46: J39.3, R39.1, U10.24
P0.47: J39.4, R40.1, U10.27
P0.48: R34.2, U10.23
P0.49: R48.1, S15.2, U13.37
P0.50: J53.1, U13.39
P0.51: J53.2, U13.41
P0.52: J54.7, U13.42
P0.53: J54.6, U13.44
P0.54: J54.5, U13.43
P0.55: J54.4, U13.46
P0.56: J54.3, U13.45
P0.58: J51.3, R49.1, U13.24
P0.59: J51.4, R50.1, U13.27
P0.60: R44.2, U13.23
P0.61: R58.1, S18.2, U16.37
P0.62: J65.1, U16.39
P0.63: J65.2, U16.41
P0.64: J66.7, U16.42
P0.65: J66.6, U16.44
P0.66: J66.5, U16.43
P0.67: J66.4, U16.46
P0.68: J66.3, U16.45
P0.70: J63.3, R59.1, U16.24
P0.71: J63.4, R60.1, U16.27
P0.72: R54.2, U16.23
P0.73: R68.1, S21.2, U19.37
P0.74: J77.1, U19.39
P0.75: J77.2, U19.41
P0.76: J78.7, U19.42
P0.77: J78.6, U19.44
P0.78: J78.5, U19.43
P0.79: J78.4, U19.46
P0.80: J78.3, U19.45
P0.82: J75.3, R69.1, U19.24
P0.83: J75.4, R70.1, U19.27
P0.84: R64.2, U19.23
P0.85: R78.1, S24.2, U22.37
P0.86: J89.1, U22.39
P0.87: J89.2, U22.41
P0.88: J90.7, U22.42
P0.89: J90.6, U22.44
P0.90: J90.5, U22.43
P0.91: J90.4, U22.46
P0.92: J90.3, U22.45
P0.94: J87.3, R79.1, U22.24
P0.95: J87.4, R80.1, U22.27
P0.96: R74.2, U22.23
P0.97: R88.1, S27.2, U25.37
P0.98: J101.1, U25.39
P0.99: J101.2, U25.41
P0.100: J102.7, U25.42
P0.101: J102.6, U25.44
P0.102: J102.5, U25.43
P0.103: J102.4, U25.46
P0.104: J102.3, U25.45
P0.106: J99.3, R89.1, U25.24
P0.107: J99.4, R90.1, U25.27
P0.108: R84.2, U25.23
P0.109: R98.1, S30.2, U28.37
P0.110: J113.1, U28.39
P0.111: J113.2, U28.41
P0.112: J114.7, U28.42
P0.113: J114.6, U28.44
P0.114: J114.5, U28.43
P0.115: J114.4, U28.46
P0.116: J114.3, U28.45
P0.118: J111.3, R99.1, U28.24
P0.119: J111.4, R100.1, U28.27
P0.120: R94.2, U28.23
P0.121: R108.1, S33.2, U31.37
P0.122: J125.1, U31.39
P0.123: J125.2, U31.41
P0.124: J126.7, U31.42
P0.125: J126.6, U31.44
P0.126: J126.5, U31.43
P0.127: J126.4, U31.46
P0.128: J126.3, U31.45
P0.130: J123.3, R109.1, U31.24
P0.131: J123.4, R110.1, U31.27
P0.132: R104.2, U31.23
P0.133: R118.1, S36.2, U34.37
P0.134: J137.1, U34.39
P0.135: J137.2, U34.41
P0.136: J138.7, U34.42
P0.137: J138.6, U34.44
P0.138: J138.5, U34.43
P0.139: J138.4, U34.46
P0.140: J138.3, U34.45
P0.142: J135.3, R119.1, U34.24
P0.143: J135.4, R120.1, U34.27
P0.144: R114.2, U34.23
SHIELD: J6.SHIELD, J6.SHIELD2, J6.SHIELD3, J6.SHIELD4, J6.SHIELD5, J6.SHIELD6, J6.SHIELD7, J6.SHIELD8, J6.SHIELD9, J6.SHIELD10
SHIELD1: J10.SHIELD, J10.SHIELD2, J10.SHIELD3, J10.SHIELD4, J10.SHIELD5, J10.SHIELD6, J10.SHIELD7, J10.SHIELD8, J10.SHIELD9, J10.SHIELD10
SHIELD2: J25.SHIELD, J25.SHIELD2, J25.SHIELD3, J25.SHIELD4, J25.SHIELD5, J25.SHIELD6, J25.SHIELD7, J25.SHIELD8, J25.SHIELD9, J25.SHIELD10
SHIELD3: J37.SHIELD, J37.SHIELD2, J37.SHIELD3, J37.SHIELD4, J37.SHIELD5, J37.SHIELD6, J37.SHIELD7, J37.SHIELD8, J37.SHIELD9, J37.SHIELD10
SHIELD4: J49.SHIELD, J49.SHIELD2, J49.SHIELD3, J49.SHIELD4, J49.SHIELD5, J49.SHIELD6, J49.SHIELD7, J49.SHIELD8, J49.SHIELD9, J49.SHIELD10
SHIELD5: J61.SHIELD, J61.SHIELD2, J61.SHIELD3, J61.SHIELD4, J61.SHIELD5, J61.SHIELD6, J61.SHIELD7, J61.SHIELD8, J61.SHIELD9, J61.SHIELD10
SHIELD6: J73.SHIELD, J73.SHIELD2, J73.SHIELD3, J73.SHIELD4, J73.SHIELD5, J73.SHIELD6, J73.SHIELD7, J73.SHIELD8, J73.SHIELD9, J73.SHIELD10
SHIELD7: J85.SHIELD, J85.SHIELD2, J85.SHIELD3, J85.SHIELD4, J85.SHIELD5, J85.SHIELD6, J85.SHIELD7, J85.SHIELD8, J85.SHIELD9, J85.SHIELD10
SHIELD8: J97.SHIELD, J97.SHIELD2, J97.SHIELD3, J97.SHIELD4, J97.SHIELD5, J97.SHIELD6, J97.SHIELD7, J97.SHIELD8, J97.SHIELD9, J97.SHIELD10
SHIELD9: J109.SHIELD, J109.SHIELD2, J109.SHIELD3, J109.SHIELD4, J109.SHIELD5, J109.SHIELD6, J109.SHIELD7, J109.SHIELD8, J109.SHIELD9, J109.SHIELD10
SHIELD10: J121.SHIELD, J121.SHIELD2, J121.SHIELD3, J121.SHIELD4, J121.SHIELD5, J121.SHIELD6, J121.SHIELD7, J121.SHIELD8, J121.SHIELD9, J121.SHIELD10
SHIELD11: J133.SHIELD, J133.SHIELD2, J133.SHIELD3, J133.SHIELD4, J133.SHIELD5, J133.SHIELD6, J133.SHIELD7, J133.SHIELD8, J133.SHIELD9, J133.SHIELD10
SWDCLK: J4.2, J8.4, U1.53
SWDCLK1: J11.2, J20.4, U4.53
SWDCLK2: J26.2, J32.4, U7.53
SWDCLK3: J38.2, J44.4, U10.53
SWDCLK4: J50.2, J56.4, U13.53
SWDCLK5: J62.2, J68.4, U16.53
SWDCLK6: J74.2, J80.4, U19.53
SWDCLK7: J86.2, J92.4, U22.53
SWDCLK8: J98.2, J104.4, U25.53
SWDCLK9: J110.2, J116.4, U28.53
SWDCLK10: J122.2, J128.4, U31.53
SWDCLK11: J134.2, J140.4, U34.53
SWDIO: J4.1, J8.2, U1.51
SWDIO1: J11.1, J20.2, U4.51
SWDIO2: J26.1, J32.2, U7.51
SWDIO3: J38.1, J44.2, U10.51
SWDIO4: J50.1, J56.2, U13.51
SWDIO5: J62.1, J68.2, U16.51
SWDIO6: J74.1, J80.2, U19.51
SWDIO7: J86.1, J92.2, U22.51
SWDIO8: J98.1, J104.2, U25.51
SWDIO9: J110.1, J116.2, U28.51
SWDIO10: J122.1, J128.2, U31.51
SWDIO11: J134.1, J140.2, U34.51
VIN: C8.1, D3.C, D4.C, J2.12, S2.3, U3.1
VIN1: C19.1, D9.C, D10.C, J16.12, S5.3, U6.1
VIN2: C30.1, D14.C, D15.C, J28.12, S8.3, U9.1
VIN3: C41.1, D19.C, D20.C, J40.12, S11.3, U12.1
VIN4: C52.1, D24.C, D25.C, J52.12, S14.3, U15.1
VIN5: C63.1, D29.C, D30.C, J64.12, S17.3, U18.1
VIN6: C74.1, D34.C, D35.C, J76.12, S20.3, U21.1
VIN7: C85.1, D39.C, D40.C, J88.12, S23.3, U24.1
VIN8: C96.1, D44.C, D45.C, J100.12, S26.3, U27.1
VIN9: C107.1, D49.C, D50.C, J112.12, S29.3, U30.1
VIN10: C118.1, D54.C, D55.C, J124.12, S32.3, U33.1
VIN11: C129.1, D59.C, D60.C, J136.12, S35.3, U36.1
VREG_EN: S2.2, U3.3
VREG_EN1: S5.2, U6.3
VREG_EN2: S8.2, U9.3
VREG_EN3: S11.2, U12.3
VREG_EN4: S14.2, U15.3
VREG_EN5: S17.2, U18.3
VREG_EN6: S20.2, U21.3
VREG_EN7: S23.2, U24.3
VREG_EN8: S26.2, U27.3
VREG_EN9: S29.2, U30.3
VREG_EN10: S32.2, U33.3
VREG_EN11: S35.2, U36.3
V_BATT: C6.1, D4.A, J1.2, J12.2, U2.3
V_BATT1: C18.1, D10.A, J19.2, J22.2, U5.3
V_BATT2: C29.1, D15.A, J31.2, J34.2, U8.3
V_BATT3: C40.1, D20.A, J43.2, J46.2, U11.3
V_BATT4: C51.1, D25.A, J55.2, J58.2, U14.3
V_BATT5: C62.1, D30.A, J67.2, J70.2, U17.3
V_BATT6: C73.1, D35.A, J79.2, J82.2, U20.3
V_BATT7: C84.1, D40.A, J91.2, J94.2, U23.3
V_BATT8: C95.1, D45.A, J103.2, J106.2, U26.3
V_BATT9: C106.1, D50.A, J115.2, J118.2, U29.3
V_BATT10: C117.1, D55.A, J127.2, J130.2, U32.3
V_BATT11: C128.1, D60.A, J139.2, J142.2, U35.3
V_USB: C5.1, D2.A, D3.A, J6.VBUS, U1.32, U2.4
V_USB1: C17.1, D8.A, D9.A, J10.VBUS, U4.32, U5.4
V_USB2: C28.1, D13.A, D14.A, J25.VBUS, U7.32, U8.4
V_USB3: C39.1, D18.A, D19.A, J37.VBUS, U10.32, U11.4
V_USB4: C50.1, D23.A, D24.A, J49.VBUS, U13.32, U14.4
V_USB5: C61.1, D28.A, D29.A, J61.VBUS, U16.32, U17.4
V_USB6: C72.1, D33.A, D34.A, J73.VBUS, U19.32, U20.4
V_USB7: C83.1, D38.A, D39.A, J85.VBUS, U22.32, U23.4
V_USB8: C94.1, D43.A, D44.A, J97.VBUS, U25.32, U26.4
V_USB9: C105.1, D48.A, D49.A, J109.VBUS, U28.32, U29.4
V_USB10: C116.1, D53.A, D54.A, J121.VBUS, U31.32, U32.4
V_USB11: C127.1, D58.A, D59.A, J133.VBUS, U34.32, U35.4
XL1: C3.2, U1.17, Y1.P$2
XL2: C7.2, U1.18, Y1.P$1
XL3: C14.2, U4.17, Y2.P$2
XL4: C15.2, U4.18, Y2.P$1
XL5: C25.2, U7.17, Y3.P$2
XL6: C26.2, U7.18, Y3.P$1
XL7: C36.2, U10.17, Y4.P$2
XL8: C37.2, U10.18, Y4.P$1
XL9: C47.2, U13.17, Y5.P$2
XL10: C48.2, U13.18, Y5.P$1
XL11: C58.2, U16.17, Y6.P$2
XL12: C59.2, U16.18, Y6.P$1
XL13: C69.2, U19.17, Y7.P$2
XL14: C70.2, U19.18, Y7.P$1
XL15: C80.2, U22.17, Y8.P$2
XL16: C81.2, U22.18, Y8.P$1
XL17: C91.2, U25.17, Y9.P$2
XL18: C92.2, U25.18, Y9.P$1
XL19: C102.2, U28.17, Y10.P$2
XL20: C103.2, U28.18, Y10.P$1
XL21: C113.2, U31.17, Y11.P$2
XL22: C114.2, U31.18, Y11.P$1
XL23: C124.2, U34.17, Y12.P$2
XL24: C125.2, U34.18, Y12.P$1
